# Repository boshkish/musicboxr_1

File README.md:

musicboxr_1
===========

radio_rpl music box r.1

This project has KiCad and Arduino IDE files for the radio_rpl music box circuit board based on the Adafruit Wave Shield r1.1.

GPL

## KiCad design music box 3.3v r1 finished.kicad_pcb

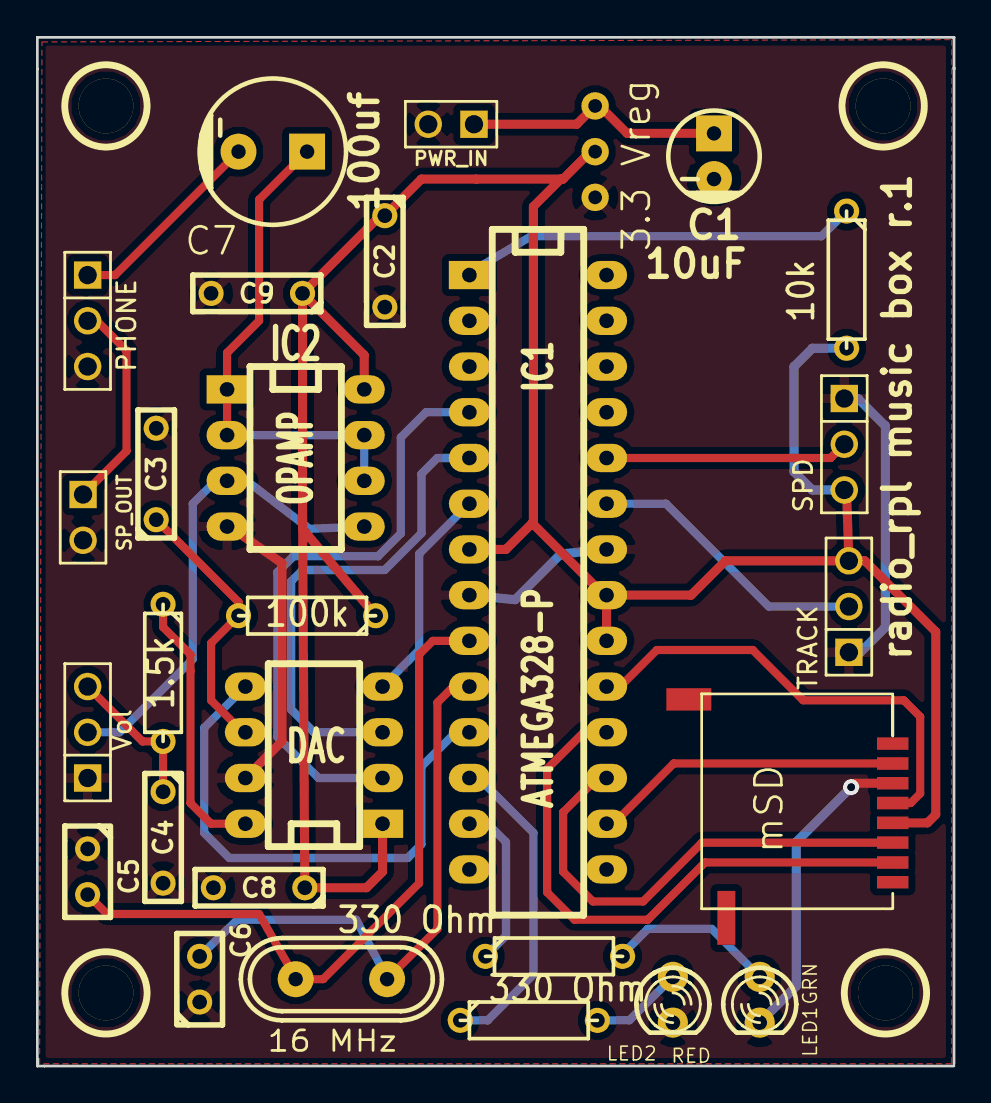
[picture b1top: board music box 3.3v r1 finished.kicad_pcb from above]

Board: 2 copper layers, 50.9 x 57.2 mm, 25 parts (0 on the bottom side), 23 nets.

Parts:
C1: 10uF; CP_5x11mm
C2, C3, C8, C9: .1 uF; C2
C4: .01 uF; C2
C5, C6: 22 pF; C1
C7: 100uf; CP_8x13mm
DAC: DIP-8__300_ELL
IC1: ATMEGA328-P; DIP-28__300_ELL
IC2: OPAMP; DIP-8__300_ELL
LED1: GRN; LED-3MM
LED2: RED; LED-3MM
PHONE: JACK_3.5MM_3PIN; PIN_ARRAY_3X1
PWR_IN: PIN_ARRAY_2X1
R1: 1.5k; R3
R2: 100k; R3
R3, R6: 330 Ohm; R3
R5: 10k; R3
SPD: PIN_ARRAY_3X1
SP_OUT: HEADER_2; PIN_ARRAY_2X1
TRACK: PIN_ARRAY_3X1
Vol: 10k; PIN_ARRAY_3X1

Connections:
DAC_CS: DAC.2, IC1.4
DAC_DI: DAC.4, IC1.6
DAC_LATCH: DAC.5, IC1.11
DAC_SCK: DAC.3, IC1.5
GND: C1.2, C2.2, C3.2, C4.2, C5.1, C6.1, C8.2, C9.2, DAC.7, IC1.8, IC1.22, IC2.4, LED1.2, LED2.2, PHONE.3, PWR_IN.2, SPD.1, SP_OUT.2, TRACK.1, Vol.1
unnamed: C4.1, R1.2, Vol.3
unnamed: PHONE.2, SP_OUT.1
unnamed: IC1.13, R3.1
unnamed: LED1.1, R3.2
unnamed: LED2.1, R6.2
unnamed: IC1.12, R6.1
unnamed: IC1.24, SPD.2
unnamed: IC2.3, IC2.5, Vol.2
unnamed: C7.1, IC2.1, IC2.2, IC2.6, IC2.7
unnamed: IC1.23, TRACK.2
unnamed: C3.1, DAC.6, R2.2
unnamed: C5.2, IC1.9
unnamed: C6.2, IC1.10
unnamed: IC1.1, R5.1
unnamed: DAC.8, R1.1
unnamed: C7.2, PHONE.1
VCC: C2.1, C8.1, C9.1, DAC.1, IC1.7, IC1.20, IC1.21, IC2.8, R2.1, R5.2, SPD.3, TRACK.3
Vin: C1.1, PWR_IN.1

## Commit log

2013-12-04 Schematic for music box circuit board r.1
2013-12-04 Board design
2013-12-04 music box r1 arduino sketch
    Based on Adafruit’s waveshield examples

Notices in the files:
music box 3.3v r1 finished.kicad_pcb:
©2013
